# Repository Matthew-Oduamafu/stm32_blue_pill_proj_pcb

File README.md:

# STM32 Blue Pill PCB Project

A KiCad-based PCB design project featuring the STM32 Blue Pill (STM32F103C8T6) microcontroller. This repository contains the full schematic, PCB layout, and rendered views of the board.

---

## Schematic

---

## PCB Layout

---

## 3D Render

### Front

### Back

---

## Project Files

| File | Description |
|------|-------------|
| `stm32_proj.kicad_sch` | KiCad schematic file |
| `stm32_proj.kicad_pcb` | KiCad PCB layout file |
| `stm32_proj.kicad_pro` | KiCad project file |
| `stm32_proj.kicad_prl` | KiCad project local settings |

## Tools Used

- [KiCad EDA](https://www.kicad.org/) — schematic capture and PCB layout

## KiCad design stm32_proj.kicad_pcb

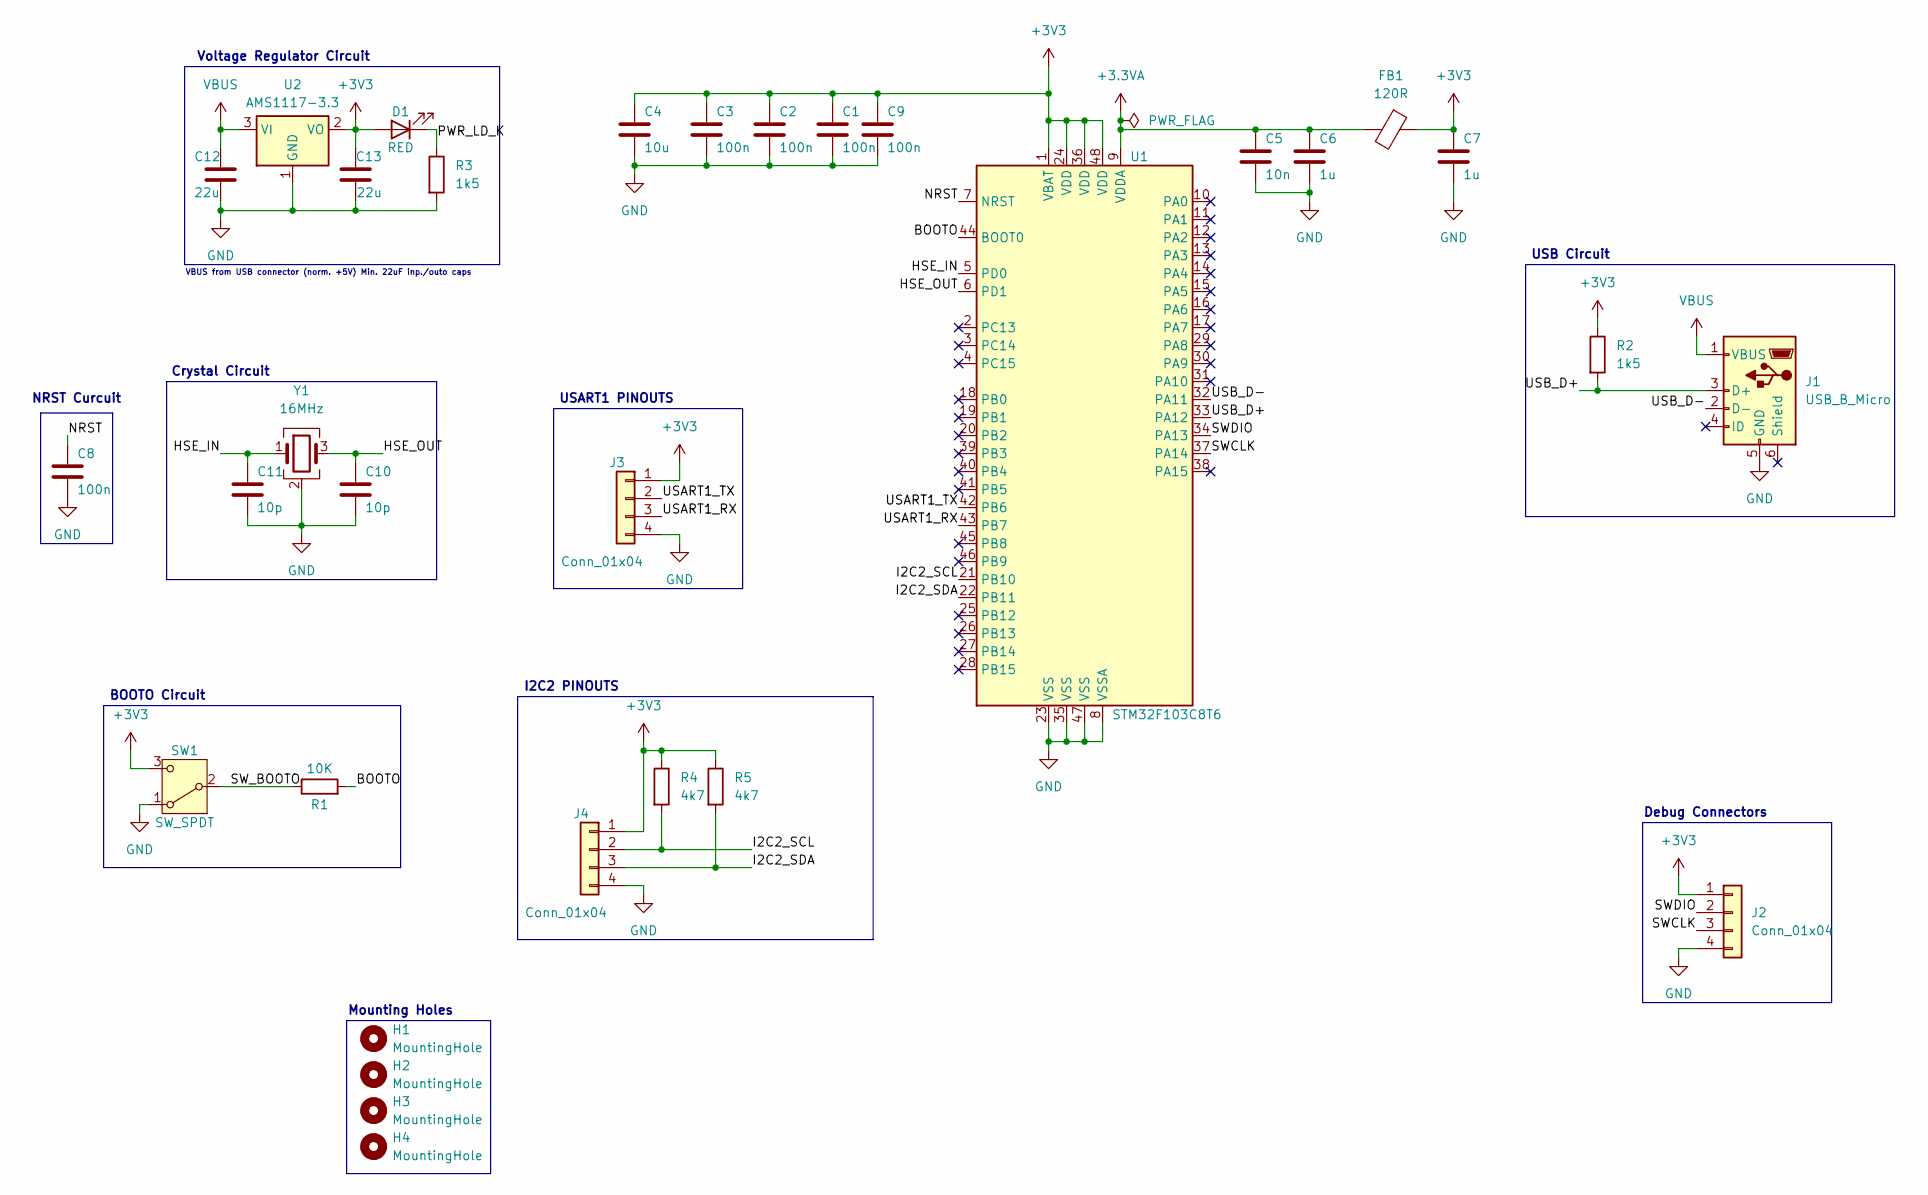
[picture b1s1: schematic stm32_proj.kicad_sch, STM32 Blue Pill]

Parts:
C1, C2, C3: 100n; C_0402_1005Metric
C4: 10u; C_0603_1608Metric
C5: 10n; C_0402_1005Metric
C6, C7: 1u; C_0402_1005Metric
C8, C9: 100n; C_0603_1608Metric
C10, C11: 10p; C_0402_1005Metric
C12, C13: 22u; C_0402_1005Metric
D1: RED; LED_0603_1608Metric
FB1: 120R; L_0201_0603Metric
H1, H2, H3, H4: MountingHole; MountingHole_2.2mm_M2
J1: USB_B_Micro; USB_Micro-B_Wuerth_629105150521
J2, J3, J4: Conn_01x04; PinHeader_1x04_P2.54mm_Vertical
R1: 10K; R_0402_1005Metric
R2, R3: 1k5; R_0402_1005Metric
R4, R5: 4k7; R_0402_1005Metric
SW1: SW_SPDT; SW_SPDT_PCM12
U1: STM32F103C8T6; LQFP-48_7x7mm_P0.5mm
U2: AMS1117-3.3; SOT-223-3_TabPin2
Y1: 16MHz; Crystal_SMD_3225-4Pin_3.2x2.5mm

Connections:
+3.3VA: C5.1, C6.1, FB1.2, U1.9 (VDDA)
+3V3: C1.1, C2.1, C3.1, C4.1, C7.1, C9.1, C13.2, D1.2 (A), FB1.1, J2.1, J3.1, J4.1, R2.1, R4.1, R5.1, SW1.3 (C), U1.1 (VBAT), U1.24 (VDD), U1.36 (VDD), U1.48 (VDD), U2.2 (VO)
/BOOTO: R1.2, U1.44 (BOOT0)
/HSE_IN: C11.1, U1.5 (PD0), Y1.1
/HSE_OUT: C10.1, U1.6 (PD1), Y1.3
/I2C2_SCL: J4.2, R4.2, U1.21 (PB10)
/I2C2_SDA: J4.3, R5.2, U1.22 (PB11)
/NRST: C8.1, U1.7 (NRST)
/PWR_LD_K: D1.1 (K), R3.1
/SWCLK: J2.3, U1.37 (PA14)
/SWDIO: J2.2, U1.34 (PA13)
/SW_BOOTO: R1.1, SW1.2 (B)
/USART1_RX: J3.3, U1.43 (PB7)
/USART1_TX: J3.2, U1.42 (PB6)
/USB_D+: J1.3 (D+), R2.2, U1.33 (PA12)
/USB_D-: J1.2 (D-), U1.32 (PA11)
GND: C1.2, C2.2, C3.2, C4.2, C5.2, C6.2, C7.2, C8.2, C9.2, C10.2, C11.2, C12.1, C13.1, J1.5 (GND), J2.4, J3.4, J4.4, R3.2, SW1.1 (A), U1.8 (VSSA), U1.23 (VSS), U1.35 (VSS), U1.47 (VSS), U2.1 (GND), Y1.2 (G), Y1.4 (G)
VBUS: C12.2, J1.1 (VBUS), U2.3 (VI)

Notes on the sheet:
NRST Curcuit
VBUS from USB connector (norm. +5V) Min. 22uF inp./outo caps
BOOTO Circuit
I2C2 PINOUTS
Mounting Holes
USB Circuit
Crystal Circuit
USART1 PINOUTS
Debug Connectors
Voltage Regulator Circuit

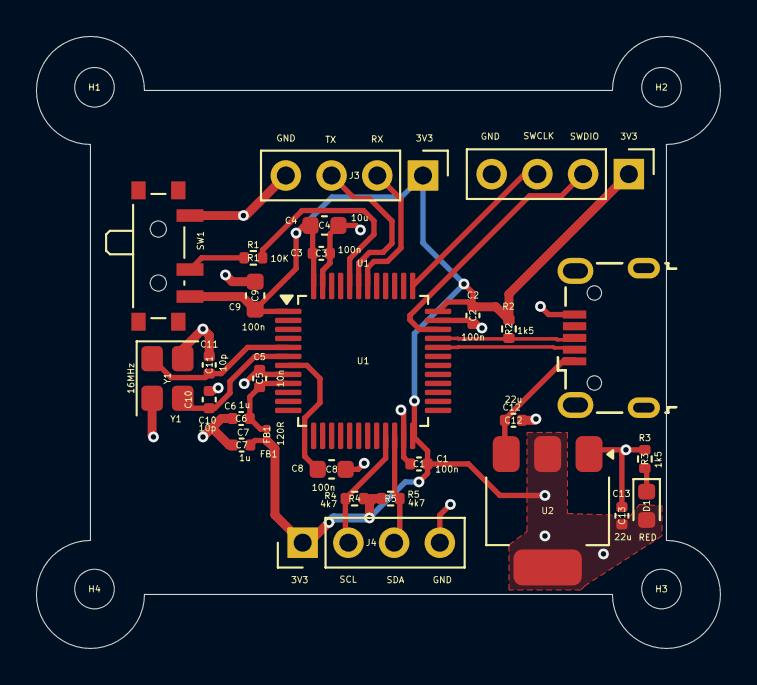
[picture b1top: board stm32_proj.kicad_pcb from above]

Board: 2 copper layers, 38.0 x 34.0 mm, 32 parts (0 on the bottom side), 18 nets.

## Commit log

2026-03-14 Initial plan
2026-03-14 Add README.md with project overview and resized images
